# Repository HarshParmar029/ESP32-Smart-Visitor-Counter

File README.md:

# ESP32 Smart Visitor Counter & Energy Saver

Bi-directional visitor counter built on the ESP32 with a custom 2-layer KiCad PCB. Two IR sensors detect entry and exit using a sequential state machine; a 0.96" I2C OLED shows the live occupancy count; a 5V opto-isolated relay switches the AC load OFF automatically when the room is empty.

Non-profit student project by Harsh, B.Tech ICT, Marwadi University, Rajkot, India.

## How it works
- Entry: Sensor A then Sensor B -> count + 1
- Exit: Sensor B then Sensor A -> count - 1 (never below 0)
- Count > 0 -> relay ON, count = 0 -> relay OFF

## Hardware
ESP32, 2x IR sensors, 0.96" I2C OLED (128x64), 5V opto-isolated relay module, USB-C 5V power input.

## PCB
KiCad, 2-layer FR-4, 1 oz copper, HASL, 120.65 mm x 66.04 mm, copper ground pours on both layers, DRC 0 errors / 0 warnings. Fabricated with PCBWay sponsorship.

## Safety
The relay switches 220V AC mains. Keep mains wiring isolated from the low-voltage section and use proper enclosure and insulation.

## Future scope
Wi-Fi cloud logging (Blynk / AWS IoT) and ToF/LiDAR sensors for side-by-side entry detection.

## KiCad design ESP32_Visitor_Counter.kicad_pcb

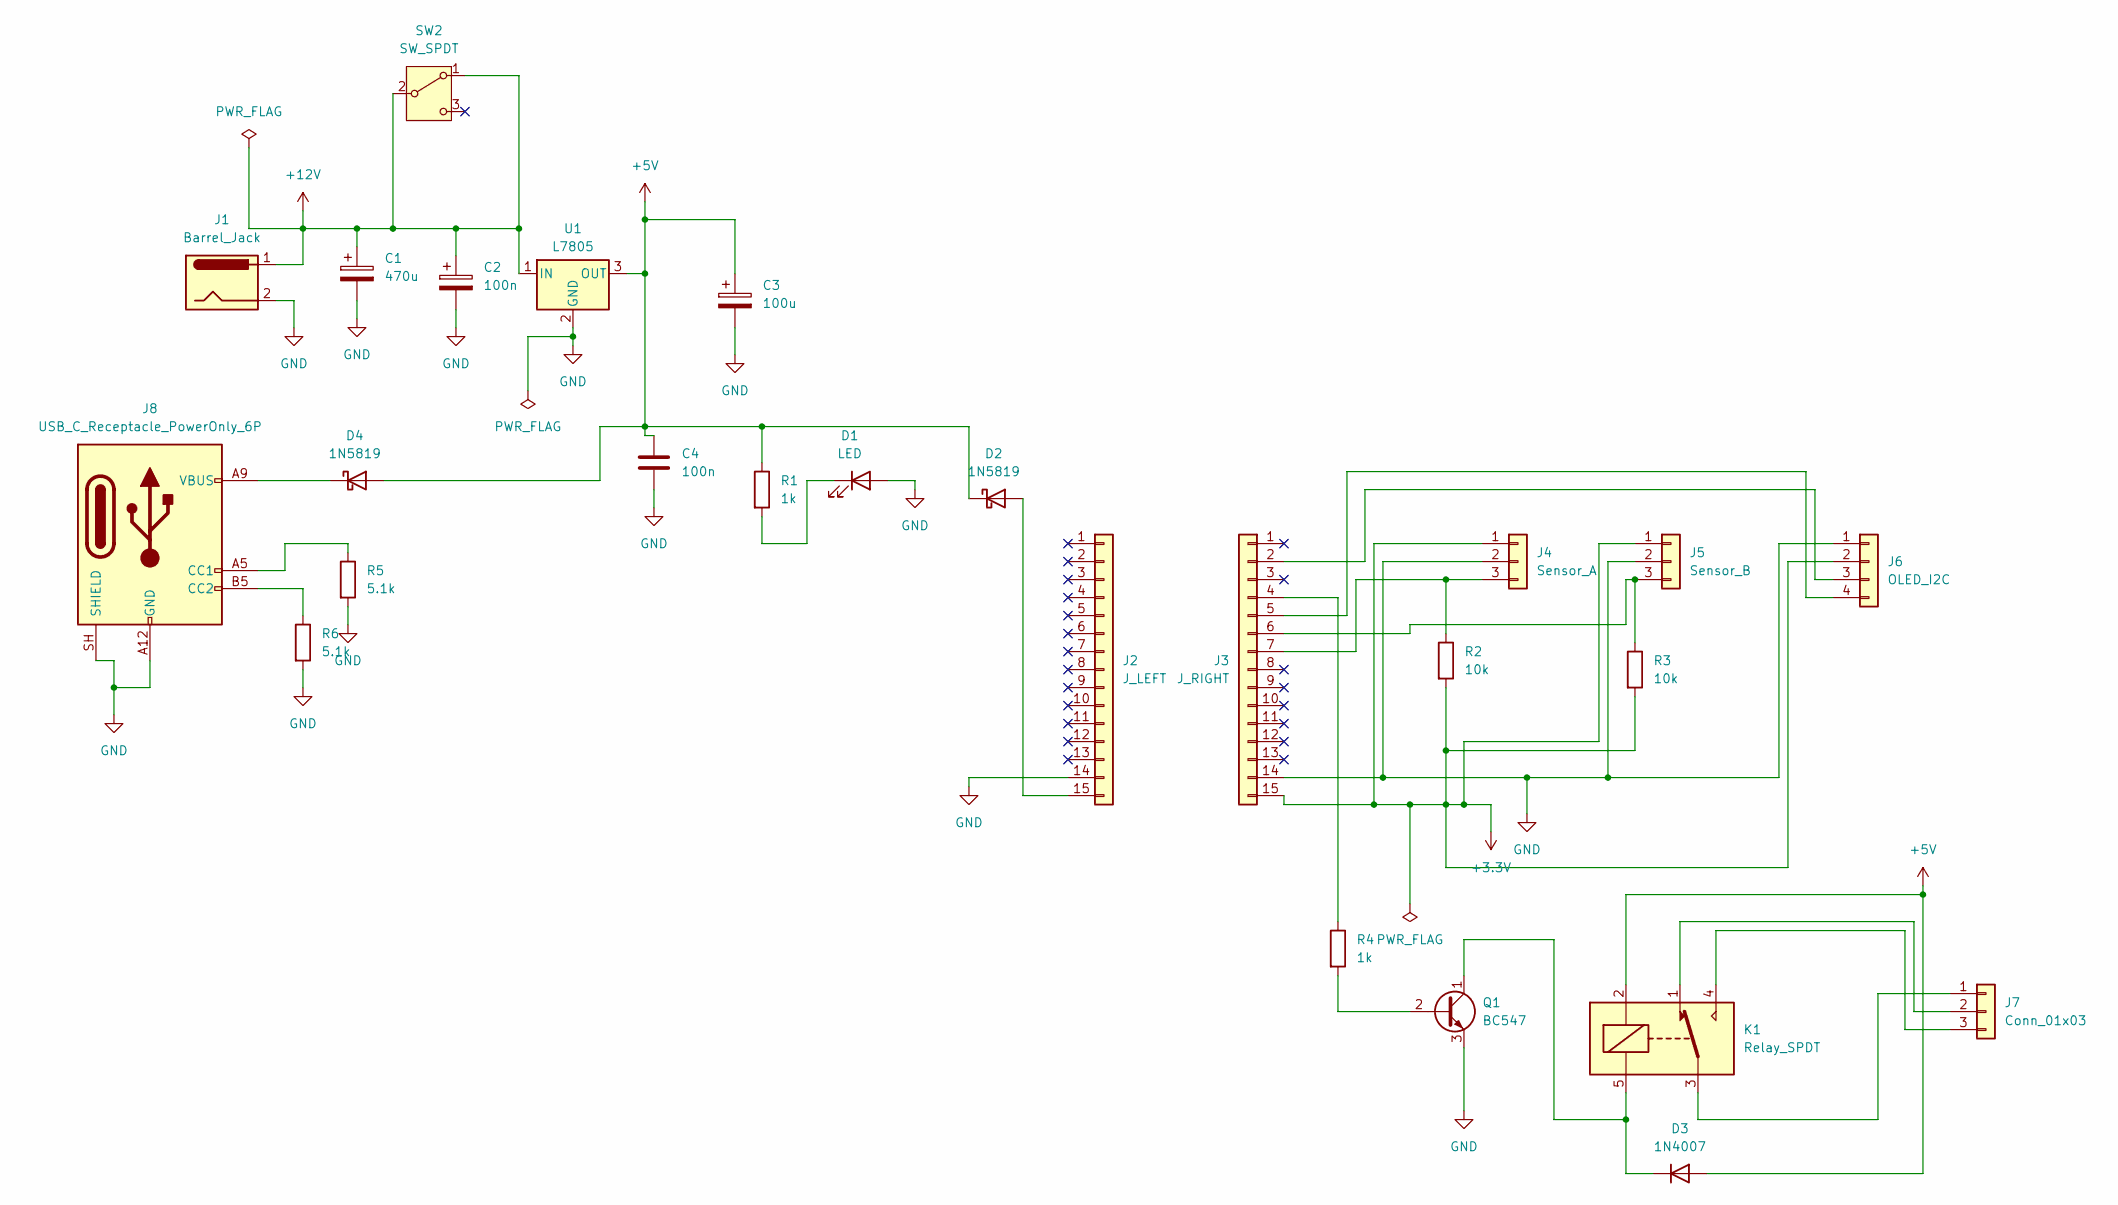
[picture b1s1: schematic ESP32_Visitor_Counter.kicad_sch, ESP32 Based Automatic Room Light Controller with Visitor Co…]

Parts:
C1: 470u; CP_Radial_Tantal_D8.0mm_P2.50mm
C2, C4: 100n; C_Disc_D3.8mm_W2.6mm_P2.50mm
C3: 100u; CP_Radial_Tantal_D8.0mm_P2.50mm
D1: LED; LED_D5.0mm
D2, D4: 1N5819; D_DO-41_SOD81_P10.16mm_Horizontal
D3: 1N4007; D_DO-41_SOD81_P10.16mm_Horizontal
J1: Barrel_Jack; BarrelJack_Horizontal
J2: J_LEFT; PinHeader_1x15_P2.54mm_Vertical
J3: J_RIGHT; PinHeader_1x15_P2.54mm_Vertical
J4: Sensor_A; PinHeader_1x03_P2.54mm_Vertical
J5: Sensor_B; PinHeader_1x03_P2.54mm_Vertical
J6: OLED_I2C; PinHeader_1x04_P2.54mm_Vertical
J7: Conn_01x03; TerminalBlock_Phoenix_MKDS-1,5-3-5.08_1x03_P5.08mm_Horizont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
J8: USB_C_Receptacle_PowerOnly_6P; USB_C_Receptacle_HRO_TYPE-C-31-M-12
K1: Relay_SPDT; Relay_SPDT_SANYOU_SRD_Series_Form_C
Q1: BC547; TO-92_Inline
R1, R4: 1k; R_Axial_DIN0207_L6.3mm_D2.5mm_P7.62mm_Horizontal
R2, R3: 10k; R_Axial_DIN0207_L6.3mm_D2.5mm_P7.62mm_Horizontal
R5, R6: 5.1k; R_Axial_DIN0207_L6.3mm_D2.5mm_P7.62mm_Horizontal
SW2: SW_SPDT; SW_Slide_SPDT_Straight_CK_OS102011MS2Q
U1: L7805; TO-220-3_Vertical

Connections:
+3.3V: J3.15, J4.1, J5.1, J6.2, R2.2, R3.2
+5V: C3.1, C4.1, D2.1 (K), D3.2 (A), D4.2 (A), K1.2, R1.1, U1.3 (OUT)
+12V: C1.1, C2.1, J1.1, SW2.1 (A), SW2.2 (B), U1.1 (IN)
GND: C1.2, C2.2, C3.2, C4.2, D1.2 (A), J1.2, J2.14, J3.14, J4.2, J5.2, J6.1, J8.A1 (GND_A12), J8.A12 (GND_A12), J8.B1 (GND_A12), J8.B12 (GND_A12), J8.SH (SHIELD_SH), Q1.3 (E), R5.2, R6.2, U1.2 (GND)
unnamed: D1.1 (K), R1.2
unnamed: D2.2 (A), J2.15
unnamed: D3.1 (K), K1.5, Q1.1 (C)
unnamed: D4.1 (K), J8.A4 (VBUS_A9), J8.A9 (VBUS_A9), J8.B4 (VBUS_A9), J8.B9 (VBUS_A9)
unnamed: J3.2, J6.3
unnamed: J3.4, R4.1
unnamed: J3.5, J6.4
unnamed: J3.6, J5.3, R3.1
unnamed: J3.7, J4.3, R2.1
unnamed: J7.1, K1.3
unnamed: J7.2, K1.1
unnamed: J7.3, K1.4
unnamed: J8.A5 (CC1_A5), R5.1
unnamed: J8.B5 (CC2_B5), R6.1
unnamed: Q1.2 (B), R4.2

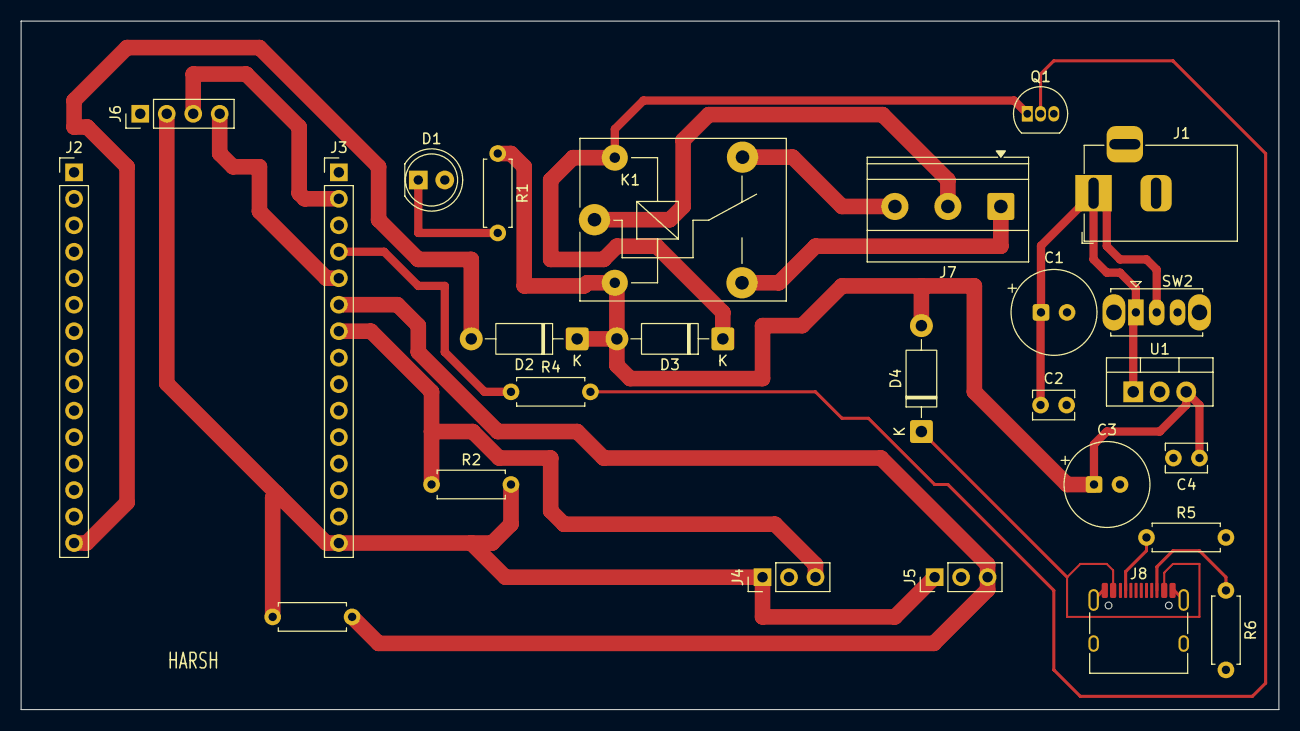
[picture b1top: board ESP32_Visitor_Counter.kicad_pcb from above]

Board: 2 copper layers, 120.7 x 66.0 mm, 26 parts (0 on the bottom side), 19 nets.
